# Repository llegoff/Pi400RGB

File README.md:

[:fr:](LISEZMOI.md) [:uk:](README.md)

# Pi400RGB
Scart/VGA interface for Raspberry Pi 400

Evolution of VGA_Zero (https://github.com/llegoff/VGA_Zero) and Pi400VGA (https://github.com/llegoff/Pi400VGA)

buy V2 on [ebay  :package: :credit_card:](https://www.ebay.fr/itm/404280189035)

### DPI (Display parallel Interface)
Like [VGA666](https://github.com/fenlogic/vga666), this pcb uses dpi interface (in mode 6 to free gpio 18 & 19)

see https://www.raspberrypi.org/documentation/hardware/raspberrypi/dpi/README.md

only the necessary bits of the dpi are redirected to the 40-pin GPIO port, with the 'gpio=2-9,12-17,20-25=a2' line on config.txt

/boot/config.txt

    # disable i2c, pin use by h-sync & v-sync
    dtparam=i2c_arm=off
    # remplace dtoverlay=vc4-kms-v3d by
    dtoverlay=vc4-fkms-v3d
    #configuration DPI
    gpio=2-9,12-17,20-24=a2
    dpi_output_format=0x6
    enable_dpi_lcd=1
    display_default_lcd=1
    dpi_group=2
    dpi_mode=16
    #---------------- dpi_mode line VGA ---------------------
    #---> 640x480 60hz    dpi_mode=4
    #---> 800x600 60hz    dpi_mode=9
    #---> 1024x768 60hz   dpi_mode=16
    #---> 1280x768 60hz   dpi_mode=23
    #---> 1280x800 60hz   dpi_mode=28
    #---> 1280x960 60hz   dpi_mode=32
    #---> 1280x1024 60hz  dpi_mode=35
    #---> 1360x768 60hz   dpi_mode=39
    #---> 1366x768 60hz   dpi_mode=81
    #---> 1400x1050 60hz  dpi_mode=42
    #---> 1440x900 60hz   dpi_mode=47
    #---> 1600x1200 60hz  dpi_mode=51
    #---> 1680x1050 60hz  dpi_mode=58
    #---> 1920x1080 60hz  dpi_mode=82
    #---> 1920x1200 60hz  dpi_mode=69
    #---> 1920x1440 60hz  dpi_mode=73    
    #--------------- dpi_mode line SCART ------------------
    dpi_mode=87
    #240p@60
    #hdmi_timings=320 1 4 30 46 240 1 4 5 14 0 0 0 60 0 6400000 1
    #288p@50
    #hdmi_timings=384 1 16 32 40 288 1 3 2 19 0 0 0 50 0 7363200 1
    #576i@50
    hdmi_timings=768 1 24 72 88 576 1 6 5 38 0 0 0 50 1 14875000 1
    #480i@60
    #hdmi_timings=640 1 24 64 104 480 1 3 6 34 0 0 0 60 1 13054080 1
    #480p@60
    #hdmi_timings=640 1 24 96 48 480 1 11 2 32 0 0 0 60 0 25452000 1

Configuration working with vc4-kms-v3d

    dtoverlay=vc4-kms-dpi-generic,rgb666-padhi
    dtparam=hactive=768,hfp=24,hsync=72,hbp=88
    dtparam=vactive=576,vfp=6,vsync=5,vbp=38
    dtparam=clock-frequency=14875000
    #   Resolution@freq  hactive hfp hsync  hbp vactive vfp vsync vbp  clock-frequency
    #VGA   640x480  @60   640     16   96    48   480    10   2    33    25175000
    #SVGA  800x600  @60   800     40  128    88   600     1   4    23    40000000
    #XGA  1024x768  @60  1024     24  136   160   768     3   6    29    65000000
    #VESA 1368x768  @60  1368     72  144   216   768     1   3    23    85860000
    #VESA 1280x800  @60  1280     64  136   200   800     1   3    24    83460000
    #VESA 1280x1024 @60  1280     48  112   248  1024     1   3    38   108000000
    #VESA 1400x1050 @60  1400     88  152   240  1050     1   3    33   122660000
    #VESA 1600x1200 @60  1600     64  192   304  1200     1   3    46   162000000
    #--- TV -----
    #240p (NTSC res)@60   320      4   30    46   240     4   5    14     6400000
    #288p (PAL res) @50   384     16   32    40   288     3   2    19     7363200
    #480p           @60   640     24   96    48   480    11   2    32    25452000
    #720p           @60  1280    110   40   220   720     5   5    20    74250000
    #1080p          @60  1920     88   44   148  1080     4   5    36   148500000
    #more timming on http://tinyvga.com/vga-timing

### Audio Interface
audio interface is connected to gpio 18 & 19 (PWM)

/boot/config.txt

    # Enable audio for PiZero(loads snd_bcm2835)
    dtoverlay=audremap,pins_18_19
    dtparam=audio=on

### Recalbox

edit the config file /crt/recalbox-crt-options.cfg in the [RECALBOX] partition mounted when you plug the SD card in your computer:

see manual : https://www.recalbox.com/recalbox-rgb-dual/manual/

edit the config file /crt/recalbox-crt-options.cfg

    # Pour recalboxrgbdual
    adapter.type = recalboxrgbdual

the first boot can take 5 minutes

https://wiki.recalbox.com/en/tutorials/video/crt/recalbox-on-crt-with-scart-dac

Add a jumper on V1 PCB

## Schematic

## PCB

## Installation
copy content of [config-example.txt](img/config-example.txt?raw=true) to /boot/config.txt

## Révision
rev1 : initial version

rev2 : add DDC on VGA connector and dip switch for recalbox configuration, coming soon

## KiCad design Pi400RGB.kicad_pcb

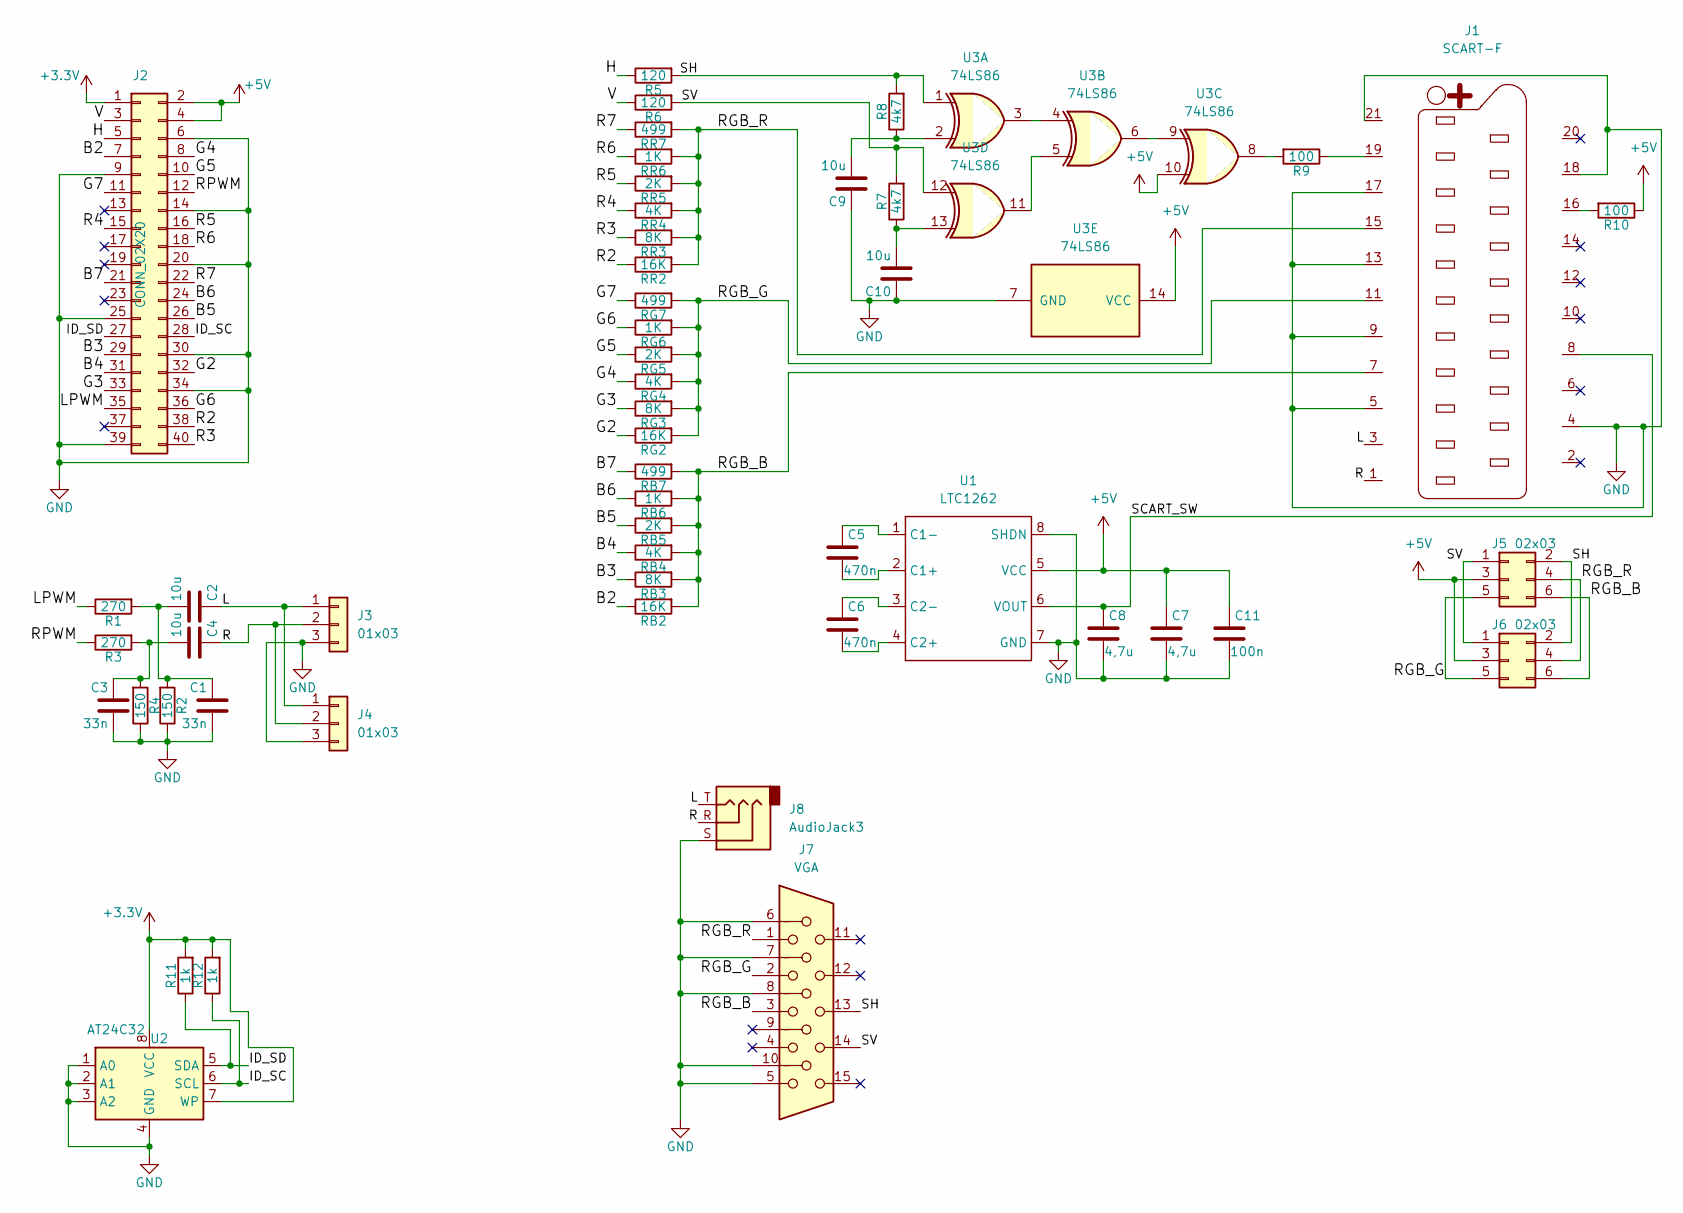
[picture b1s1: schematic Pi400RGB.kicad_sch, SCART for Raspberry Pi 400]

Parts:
C1, C3: 33n; C_0805_2012Metric
C2, C4, C9, C10: 10u; C_0805_2012Metric
C5, C6: 470n; C_0805_2012Metric
C7, C8: 4,7u; C_0805_2012Metric
C11: 100n; C_0805_2012Metric
J1: SCART-F; SCART
J2: CONN_02X20; 2x40_PCB
J3, J4: 01x03; PinHeader_1x03_P2.54mm_Vertical
J5, J6: 02x03; PinHeader_2x03_P2.54mm_Vertical
J7: VGA; DB_15F-VGA
J8: AudioJack3; jack3.5smd
R1, R3: 270; R_0805_2012Metric
R2, R4: 150; R_0805_2012Metric
R5, R6: 120; R_0805_2012Metric
R7, R8: 4k7; R_0805_2012Metric
R9, R10: 100; R_0805_2012Metric
R11, R12: 1k; R_0805_2012Metric
RB2: 16K; R_0805_2012Metric
RB3: 8K; R_0805_2012Metric
RB4: 4K; R_0805_2012Metric
RB5: 2K; R_0805_2012Metric
RB6: 1K; R_0805_2012Metric
RB7: 499; R_0805_2012Metric
RG2: 16K; R_0805_2012Metric
RG3: 8K; R_0805_2012Metric
RG4: 4K; R_0805_2012Metric
RG5: 2K; R_0805_2012Metric
RG6: 1K; R_0805_2012Metric
RG7: 499; R_0805_2012Metric
RR2: 16K; R_0805_2012Metric
RR3: 8K; R_0805_2012Metric
RR4: 4K; R_0805_2012Metric
RR5: 2K; R_0805_2012Metric
RR6: 1K; R_0805_2012Metric
RR7: 499; R_0805_2012Metric
U1: LTC1262; SOIC-8_3.9x4.9mm_P1.27mm
U2: AT24C32; SOIC-8_3.9x4.9mm_P1.27mm
U3: 74LS86; SOIC-14_3.9x8.7mm_P1.27mm

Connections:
+3V3: J2.1, R11.2, R12.2, U2.7 (WP), U2.8 (VCC)
+5V: C7.1, C11.1, J2.2, J2.4, J5.3, J6.3, R10.1, U1.5 (VCC), U3.10, U3.14 (VCC)
/B2: J2.7, RB2.1
/B3: J2.29, RB3.1
/B4: J2.31, RB4.1
/B5: J2.26, RB5.1
/B6: J2.24, RB6.1
/B7: J2.21, RB7.1
/G2: J2.32, RG2.1
/G3: J2.33, RG3.1
/G4: J2.8, RG4.1
/G5: J2.10, RG5.1
/G6: J2.36, RG6.1
/G7: J2.11, RG7.1
/H: J2.5, R5.1
/ID_SC: J2.28, R12.1, U2.6 (SCL)
/ID_SD: J2.27, R11.1, U2.5 (SDA)
/L: C2.1, J1.3, J3.1, J4.1, J8.T
/LPWM: J2.35, R1.1
/R: C4.1, J1.1, J3.2, J4.2, J8.R
/R2: J2.38, RR2.1
/R3: J2.40, RR3.1
/R4: J2.15, RR4.1
/R5: J2.16, RR5.1
/R6: J2.18, RR6.1
/R7: J2.22, RR7.1
/RGB_B: J1.7, J5.6, J6.6, J7.3, RB2.2, RB3.2, RB4.2, RB5.2, RB6.2, RB7.2
/RGB_G: J1.11, J5.5, J6.5, J7.2, RG2.2, RG3.2, RG4.2, RG5.2, RG6.2, RG7.2
/RGB_R: J1.15, J5.4, J6.4, J7.1, RR2.2, RR3.2, RR4.2, RR5.2, RR6.2, RR7.2
/RPWM: J2.12, R3.1
/SCART_SW: C8.1, J1.8, U1.6 (VOUT)
/SH: J5.2, J6.2, J7.13, R5.2, R8.2, U3.1
/SV: J5.1, J6.1, J7.14, R6.2, R7.2, U3.12
/V: J2.3, R6.1
GND: C1.2, C3.2, C7.2, C8.2, C9.1, C10.1, C11.2, J1.4, J1.5, J1.9, J1.13, J1.17, J1.18, J1.21, J2.6, J2.9, J2.14, J2.20, J2.25, J2.30, J2.34, J2.39, J3.3, J4.3, J7.5, J7.6, J7.7, J7.8, J7.10, J8.S, R2.1, R4.1, U1.7 (GND), U1.8 (SHDN), U2.1 (A0), U2.2 (A1), U2.3 (A2), U2.4 (GND), U3.7 (GND)
unnamed: C1.1, C2.2, R1.2, R2.2
unnamed: C3.1, C4.2, R3.2, R4.2
unnamed: C5.1, U1.1 (C1-)
unnamed: C5.2, U1.2 (C1+)
unnamed: C6.1, U1.3 (C2-)
unnamed: C6.2, U1.4 (C2+)
unnamed: C9.2, R8.1, U3.2
unnamed: C10.2, R7.1, U3.13
unnamed: J1.16, R10.2
unnamed: J1.19, R9.1
unnamed: R9.2, U3.8
unnamed: U3.3, U3.4
unnamed: U3.6, U3.9
unnamed: U3.5, U3.11

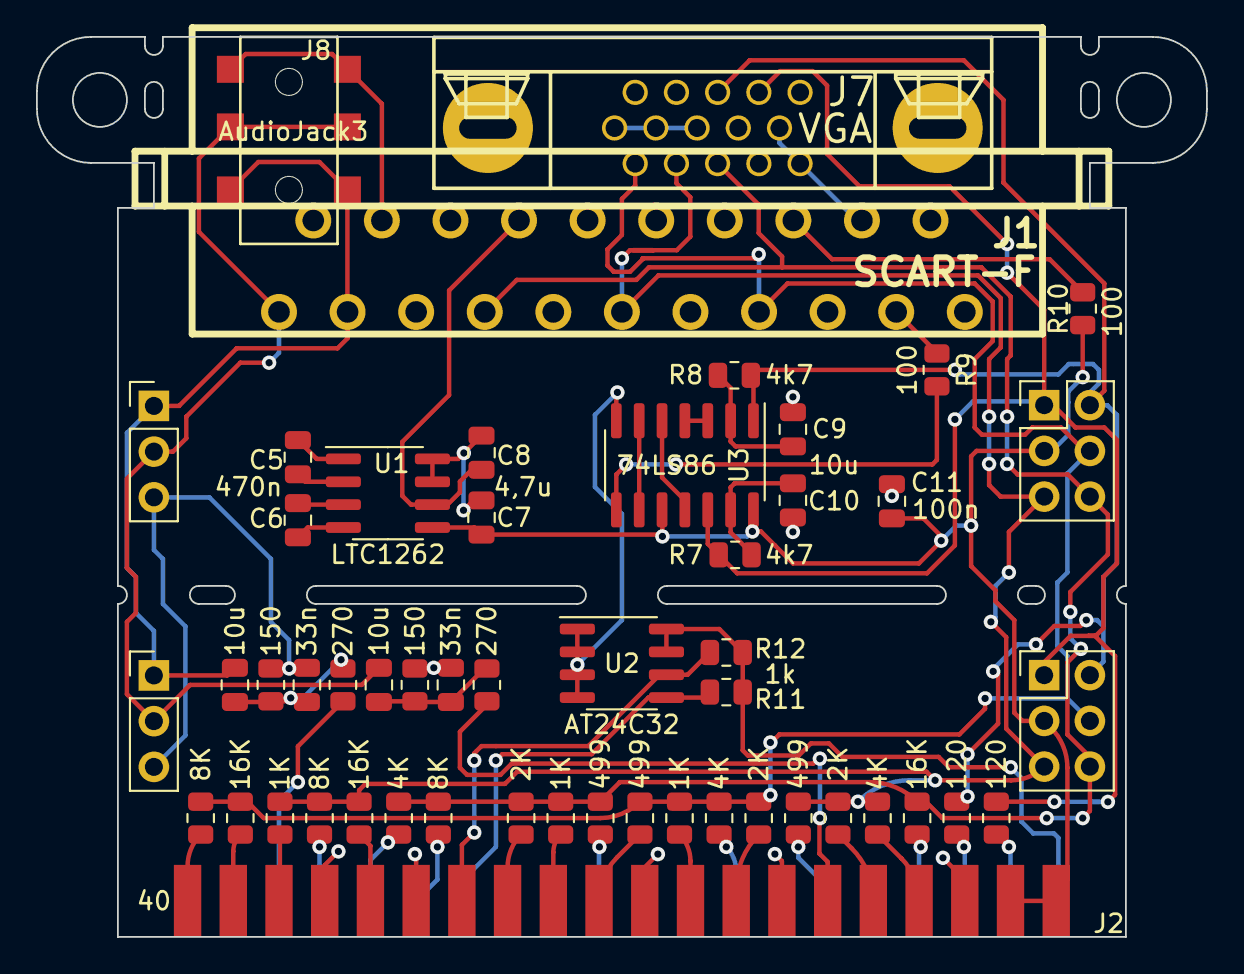
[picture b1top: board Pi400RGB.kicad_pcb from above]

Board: 2 copper layers, 65.0 x 50.0 mm, 52 parts (0 on the bottom side), 49 nets.
